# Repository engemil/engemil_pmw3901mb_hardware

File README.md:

# EngEmil PMW3901MB Optical Flow Sensor Module

The EngEmil PMW3901MB Module is a Optical Motion Tracking Chip module, for optical position control of drones. The PCB module is designed with KiCAD 9.

## Versions

**Version 2**
- Removed 3v3 regulator and changed VCC pin text to 3V3
- Added ESD protection
- Added reverse voltage protection
- Added pull-up resistors for SCLK and MISO. Marked as not mounted.
- Added resistor for RC-filter for PMW3901MB. Marked as R4=0ohm, and C3 and C4 not mounted. Note added in schematic.

**Version 1**
- First prototype
- 3v3 regulator and 1v8 regulator
- Standard pins
- 2 mounting holes

## Links

- PMW3901MB-TXQT https://www.pixart.com/products-detail/44/PMW3901MB-TXQT
- Generating Gerbers (Manufacturer Recommendations): https://docs.oshpark.com/design-tools/kicad/generating-kicad-gerbers/
- Design Rule (Manufacturer Recommendations):
    - https://docs.oshpark.com/design-tools/kicad/kicad-design-rules/
    - https://www.pcbway.com/pcb_prototype/Pinted_Circuit_Board_Prototype.html
    - https://www.pcbway.com/capabilities.html
    - https://jlcpcb.com/capabilities/pcb-capabilities

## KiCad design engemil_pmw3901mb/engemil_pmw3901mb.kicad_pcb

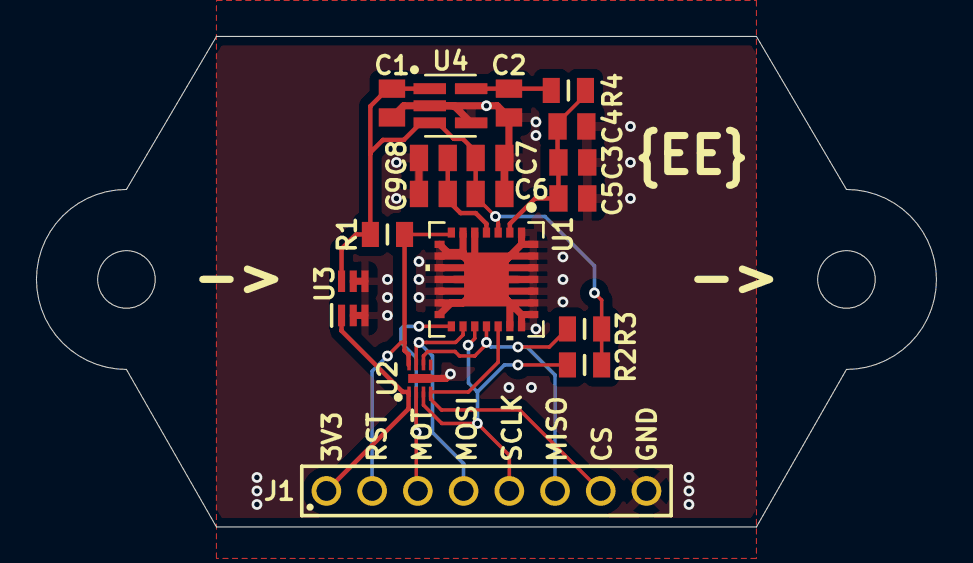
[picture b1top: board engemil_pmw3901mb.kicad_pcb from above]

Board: 2 copper layers, 50.0 x 27.2 mm, 20 parts (0 on the bottom side), 12 nets.

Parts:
C1, C2: 1uF; CAPC2012X110N
C3, C4: Not Mount; CAPC2012X110N
C5, C6, C8: 0.1uF; CAPC2012X110N
C7: 10uF; CAPC2012X110N
C9: 4.7uF; CAPC2012X110N
H1, H2: MountingHole; MountingHole_3.2mm_M3_ISO14580
J1: 6130XX11121; 61300811121
R1: 10kOhm; RESC2012X60N
R2, R3: Not Mount; RESC2012X60N
R4: 0Ohm; RESC2012X60N
U1: PMW3901MB-TXQT; QFN_01MB-TXQT_PIX-M
U2: TPD8E003DQDR; SON40P135X170X80-9N
U3: LM66100QDCKRQ1; SOT65P210X110-6N
U4: TLV77318PDBVR; DBV0005A-IPC_A

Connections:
+1V8: C2.2, R4.1, U4.5 (OUT)
+3.3V: C1.2, C6.1, C7.1, R1.1, R2.1, R3.1, U1.3 (VDDIO), U3.6 (VOUT), U4.1 (IN), U4.3 (EN)
CS: J1.7, U1.19 (NCS), U2.4 (IO4)
GND: C1.1, C2.1, C3.2, C4.2, C5.2, C6.2, C7.2, C8.2, C9.2, J1.8, U1.1 (GND), U1.5 (NC), U1.6 (NC), U1.8 (NC), U1.9 (NC), U1.10 (NC), U1.11 (NC), U1.12 (NC), U1.13 (NC), U1.14 (NC), U1.20 (NC), U1.21 (GND), U1.22 (NC), U1.23 (NC), U1.24 (NC), U1.25 (NC), U1.26 (NC), U1.27 (NC), U1.28 (NC), U1.29 (GND), U2.9 (EP/GND), U3.2 (GND), U3.3 (~CE), U3.4 (N/C), U3.5 (ST), U4.2 (GND), U4.4 (NC)
MISO: J1.6, R3.2, U1.18 (MISO), U2.6 (IO6)
MOSI: J1.4, U1.16 (MOSI), U2.7 (IO7)
MOTION: J1.3, U1.15 (MOTION), U2.2 (IO2)
unnamed: C3.1, C4.1, C5.1, R4.2, U1.2 (VDD)
unnamed: C8.1, C9.1, U1.4 (VREG)
RESET: J1.2, R1.2, U1.7 (NRESET), U2.8 (IO8)
SCLK: J1.5, R2.2, U1.17 (SCLK), U2.3 (IO3)
VCC: J1.1, U2.1 (IO1), U3.1 (VIN)

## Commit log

2025-06-06 Added license and base kicad project
2025-06-08 Added docs folder with datasheet, added info in title block of schematic, added info in readme
2025-06-09 - Added BOM file - Added datasheets under docs folder - Added symbol, footprint and 3d models to lib - Added readme files to subfolder of lib - Added raw folder for lib - Designed voltage regulators 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
2025-06-10 Updated bom and raw files
2025-06-10 - Added more components to the BOM - Added component EDA/CAD files to the lib folder - Finished first version of Schematic
2025-06-11 - Updated Schematic date - First orientation of components in pcb editor
2025-06-11 - Updated notes in schematic - Updated PMW3901MB NCS pin fron not connected to unspecified - Updated component orientation in PCB editor
2025-06-11 Updated schematic and pcb
2025-06-12 - Added mounting holes in Schematic and PCB - Finished traces and top and bottom ground plains - Added vias for copper islands / isolated copper - Generated pdf of schematic and pcb - Updated README 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
2025-06-12 - Added gerber files - Updated text on bottom silk layer - Updated images for readme file - Updated PCB PDF file
2025-06-23 Added 3 new components
2025-06-24 - Removed 3v3 voltage regulator and two capacitors - Changed reference designators (C1,C2,...,U2,U3,...) - Added R4 - Marked C3 and C4 as not mount - Added comment about RC filter - Added pull-up res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
2025-06-24 - Finalized version 2 - Updated PCB pdf file - Updated README - Updated images - Updated PCB design - Updated gerber files
2025-06-25 Corrected BOM for version 2
2025-06-26 Renamed gerbers zip file to include version in name
2025-06-26 - Updated Schematic date - Corrected schematic pdf file to match latest updates
2025-06-26 Corrected schematic pdf from portrait to landscape orientation

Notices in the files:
engemil_pmw3901mb/engemil_pmw3901mb.kicad_pcb:
Licensed under CERN-OHL-W-2.0
